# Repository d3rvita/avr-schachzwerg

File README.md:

# AVR-Schachzwerg

The AVR-Schachzwerg is a dedicated chess computer based on the 8-bit microcontroller ATmega88. It is very minimalist like its siblings from the late '70s and the early '80s. Four digit 7-segment display, some buttons and a µC, that's it.

AVR-Schachzwerg was originally developed in 2008 by Andre Adrian, he named it "SHAH". In 2009 (or so) Elektor designed and distributed a PCB of this chess computer (aka "AVR-Max Schachcomputer"). But the button layout was just awful and there ware neither a voltage regulator nor connectors for power supply included. So I attempted to make a better PCB layout... 

Schematic is pretty much originally. I only lowered the resistor values for more display brightness and inserted a voltage regulator together with two connectors for power supply. It can be powered either via USB or a ordinary 8-12 VDC power supply (5.5mm / 2.1mm, plus inside).

The program is a adapted version of Micro-Max 4.8. That is a chess engine by H.G. Müller consisting of less than 2000 characters of C code. Playing strength is around 1300 Elo on the www.schachcomputer.info rating list.

EAGLE was used for creating the schematic (schachzwerg.sch) and layout (schachzwerg.brd). gerber-schachzwerg.zip contains all needed gerber files for PCB production. Bill of material is listed in schachzwerg-bom.txt. All components are designed as THT for easy assembly. It is highly recommended using a socket for the µC. __In order to prevent side effects or even damage don't feed both power supply connectors simultaneously!__

## Schematic

## PCB

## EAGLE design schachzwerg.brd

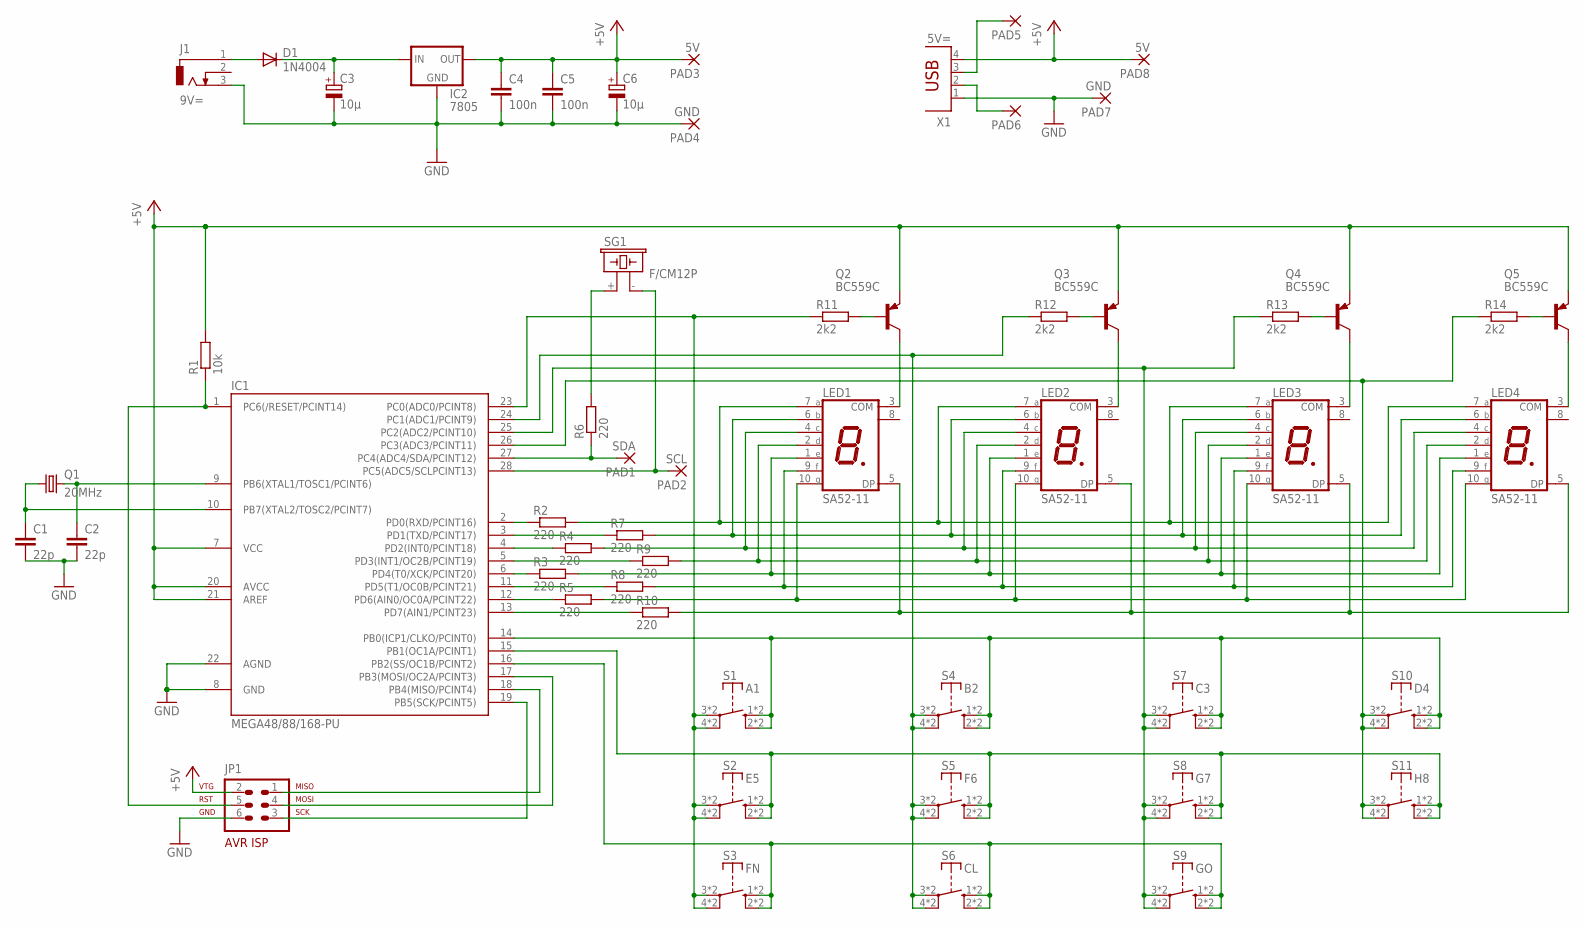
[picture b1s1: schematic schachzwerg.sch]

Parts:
C1, C2: 22p; C025-025X050
C3, C6: 10µ; E2,5-5
C4, C5: 100n; C025-025X050
D1: 1N4004; DO41-10
IC1: MEGA48/88/168-PU; DIL28-3
IC2: 7805; 78XXS
J1: 9V=; DCJ0303
JP1: AVR-ISP-6
LED1, LED2, LED3, LED4: SA52-11
PAD1: SDA; 1,6/0,8
PAD2: SCL; 1,6/0,8
PAD3, PAD8: 5V; 1,6/0,8
PAD4, PAD7: GND; 1,6/0,8
PAD5, PAD6: 1,6/0,8
Q1: 20MHz; HC49/S
Q2, Q3, Q4, Q5: BC559C; TO92-EBC
R1: 10k; 0204/7
R2, R3, R4, R5, R6, R7, R8, R9, R10: 220; 0204/7
R11, R12, R13, R14: 2k2; 0204/7
S1: A1; DT6
S2: E5; DT6
S3: FN; DT6
S4: B2; DT6
S5: F6; DT6
S6: CL; DT6
S7: C3; DT6
S8: G7; DT6
S9: GO; DT6
S10: D4; DT6
S11: H8; DT6
SG1: F/CM12P
X1: 5V=; PN87520

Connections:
+5V: C4.1, C5.1, C6.+, IC1.7 (VCC), IC1.20 (AVCC), IC1.21 (AREF), IC2.OUT, JP1.2, PAD3.1, PAD8.1, Q2.E, Q3.E, Q4.E, Q5.E, R1.2, X1.4
GND: C1.2, C2.2, C3.-, C4.2, C5.2, C6.-, IC1.8 (GND), IC1.22 (AGND), IC2.GND, J1.3, JP1.6, PAD4.1, PAD7.1, X1.1
unnamed: IC1.2 (PD0(RXD/PCINT16)), R2.1
unnamed: IC1.3 (PD1(TXD/PCINT17)), R7.1
unnamed: IC1.4 (PD2(INT0/PCINT18)), R4.1
unnamed: IC1.5 (PD3(INT1/OC2B/PCINT19)), R9.1
unnamed: IC1.6 (PD4(T0/XCK/PCINT20)), R3.1
unnamed: IC1.11 (PD5(T1/OC0B/PCINT21)), R8.1
unnamed: IC1.12 (PD6(AIN0/OC0A/PCINT22)), R5.1
unnamed: IC1.13 (PD7(AIN1/PCINT23)), R10.1
unnamed: LED1.7 (A), LED2.7 (A), LED3.7 (A), LED4.7 (A), R2.2
unnamed: LED1.6 (B), LED2.6 (B), LED3.6 (B), LED4.6 (B), R7.2
unnamed: LED1.4 (C), LED2.4 (C), LED3.4 (C), LED4.4 (C), R4.2
unnamed: LED1.2 (D), LED2.2 (D), LED3.2 (D), LED4.2 (D), R9.2
unnamed: LED1.1 (E), LED2.1 (E), LED3.1 (E), LED4.1 (E), R3.2
unnamed: LED1.9 (F), LED2.9 (F), LED3.9 (F), LED4.9 (F), R8.2
unnamed: LED1.10 (G), LED2.10 (G), LED3.10 (G), LED4.10 (G), R5.2
unnamed: LED1.5 (DP), LED2.5 (DP), LED3.5 (DP), LED4.5 (DP), R10.2
unnamed: LED1.3 (COM), Q2.C
unnamed: LED2.3 (COM), Q3.C
unnamed: LED3.3 (COM), Q4.C
unnamed: LED4.3 (COM), Q5.C
unnamed: Q2.B, R11.2
unnamed: Q3.B, R12.2
unnamed: Q4.B, R13.2
unnamed: Q5.B, R14.2
unnamed: C2.1, IC1.9 (PB6(XTAL1/TOSC1/PCINT6)), Q1.2
unnamed: PAD6.1, X1.2
unnamed: R6.2, SG1.+ (1)
unnamed: IC1.28 (PC5(ADC5/SCLPCINT13)), PAD2.1, SG1.- (2)
unnamed: D1.A, J1.1
unnamed: IC1.1 (PC6(/RESET/PCINT14)), JP1.5, R1.1
unnamed: IC1.19 (PB5(SCK/PCINT5)), JP1.3
unnamed: IC1.17 (PB3(MOSI/OC2A/PCINT3)), JP1.4
unnamed: IC1.18 (PB4(MISO/PCINT4)), JP1.1
unnamed: IC1.23 (PC0(ADC0/PCINT8)), R11.1, S1.3, S1.4, S1.7, S1.8, S2.3, S2.4, S2.7, S2.8, S3.3, S3.4, S3.7, S3.8
unnamed: IC1.24 (PC1(ADC1/PCINT9)), R12.1, S4.3, S4.4, S4.7, S4.8, S5.3, S5.4, S5.7, S5.8, S6.3, S6.4, S6.7, S6.8
unnamed: IC1.25 (PC2(ADC2/PCINT10)), R13.1, S7.3, S7.4, S7.7, S7.8, S8.3, S8.4, S8.7, S8.8, S9.3, S9.4, S9.7, S9.8
unnamed: IC1.26 (PC3(ADC3/PCINT11)), R14.1, S10.3, S10.4, S10.7, S10.8, S11.3, S11.4, S11.7, S11.8
unnamed: IC1.14 (PB0(ICP1/CLKO/PCINT0)), S1.1 (S), S1.2 (S), S1.5 (S), S1.6 (S), S4.1 (S), S4.2 (S), S4.5 (S), S4.6 (S), S7.1 (S), S7.2 (S), S7.5 (S), S7.6 (S), S10.1 (S), S10.2 (S), S10.5 (S), S10.6 (S)
unnamed: PAD5.1, X1.3
unnamed: IC1.15 (PB1(OC1A/PCINT1)), S2.1 (S), S2.2 (S), S2.5 (S), S2.6 (S), S5.1 (S), S5.2 (S), S5.5 (S), S5.6 (S), S8.1 (S), S8.2 (S), S8.5 (S), S8.6 (S), S11.1 (S), S11.2 (S), S11.5 (S), S11.6 (S)
unnamed: IC1.16 (PB2(SS/OC1B/PCINT2)), S3.1 (S), S3.2 (S), S3.5 (S), S3.6 (S), S6.1 (S), S6.2 (S), S6.5 (S), S6.6 (S), S9.1 (S), S9.2 (S), S9.5 (S), S9.6 (S)
unnamed: C3.+, D1.C, IC2.IN
unnamed: C1.1, IC1.10 (PB7(XTAL2/TOSC2/PCINT7)), Q1.1
unnamed: IC1.27 (PC4(ADC4/SDA/PCINT12)), PAD1.1, R6.1

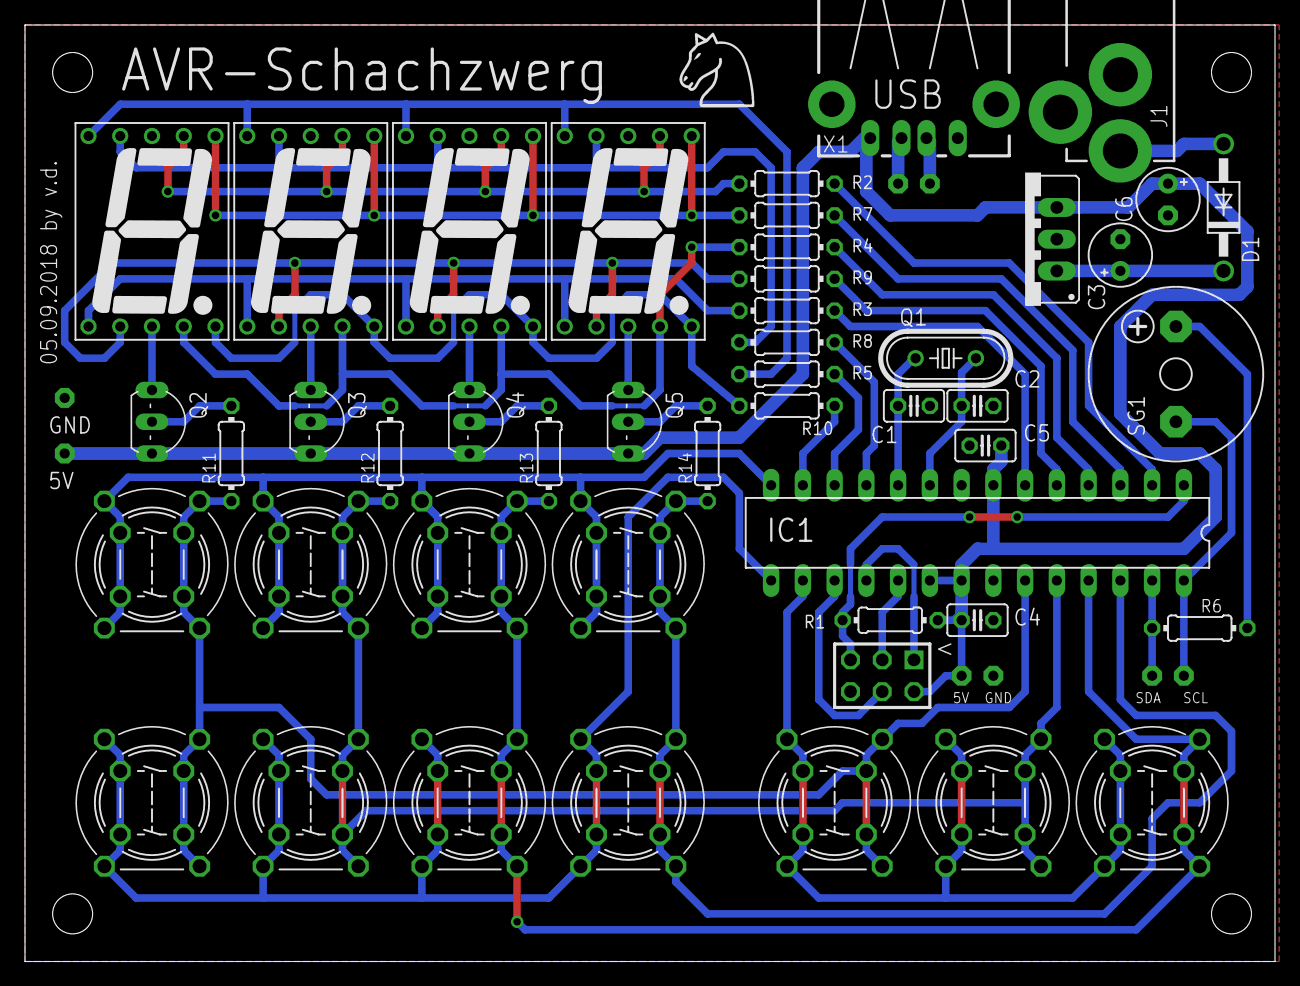
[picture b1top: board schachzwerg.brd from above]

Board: 2 copper layers, 100.0 x 74.9 mm, 55 parts (0 on the bottom side), 46 nets.

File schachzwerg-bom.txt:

Part       Value               Device             Package        Description                                                 
C1*        22p                 C-EU025-025X050    C025-025X050   CAPACITOR, European symbol                                  
C2*        22p                 C-EU025-025X050    C025-025X050   CAPACITOR, European symbol                                  
C3         10µ                 CPOL-EUE2.5-5      E2,5-5         POLARIZED CAPACITOR, European symbol                        
C4         100n                C-EU025-025X050    C025-025X050   CAPACITOR, European symbol                                  
C5         100n                C-EU025-025X050    C025-025X050   CAPACITOR, European symbol                                  
C6         10µ                 CPOL-EUE2.5-5      E2,5-5         POLARIZED CAPACITOR, European symbol                        
D1         1N4004              1N4004             DO41-10        DIODE                                                       
IC1**      MEGA48/88/168-PU    MEGA48/88/168-PU   DIL28-3        MICROCONTROLLER                                             
IC2        7805                78XXS              TO220          VOLTAGE REGULATOR                                           
J1         9V=                 DCJ0303            DCJ0303        DC POWER JACK (5.5mm / 2.1mm)                               
JP1        AVR-ISP-6           AVR-ISP-6          AVR-ISP-6      AVR ISP-6 Serial Programming Header                         
LED1       SA52-11             7-SEG_SA52-11      SA52-11        Kingbright 14.2mm (0.56 INCH) SINGLE DIGIT NUMERIC DUISPLAY 
LED2       SA52-11             7-SEG_SA52-11      SA52-11        Kingbright 14.2mm (0.56 INCH) SINGLE DIGIT NUMERIC DUISPLAY 
LED3       SA52-11             7-SEG_SA52-11      SA52-11        Kingbright 14.2mm (0.56 INCH) SINGLE DIGIT NUMERIC DUISPLAY 
LED4       SA52-11             7-SEG_SA52-11      SA52-11        Kingbright 14.2mm (0.56 INCH) SINGLE DIGIT NUMERIC DUISPLAY 
Q1*        20MHz               CRYSTAL            HC49/S         CRYSTAL                                                     
Q2         BC559C              BC559C             TO92-EBC       PNP Transistor                                             
Q3         BC559C              BC559C             TO92-EBC       PNP Transistor                                             
Q4         BC559C              BC559C             TO92-EBC       PNP Transistor                                             
Q5         BC559C              BC559C             TO92-EBC       PNP Transistor                                             
R1         10k                 R-EU_0204/7        0204/7         RESISTOR, European symbol                                   
R2         220                 R-EU_0204/7        0204/7         RESISTOR, European symbol                                   
R3         220                 R-EU_0204/7        0204/7         RESISTOR, European symbol                                   
R4         220                 R-EU_0204/7        0204/7         RESISTOR, European symbol                                   
R5         220                 R-EU_0204/7        0204/7         RESISTOR, European symbol                                   
R6***      220                 R-EU_0204/7        0204/7         RESISTOR, European symbol                                   
R7         220                 R-EU_0204/7        0204/7         RESISTOR, European symbol                                   
R8         220                 R-EU_0204/7        0204/7         RESISTOR, European symbol                                   
R9         220                 R-EU_0204/7        0204/7         RESISTOR, European symbol                                   
R10        220                 R-EU_0204/7        0204/7         RESISTOR, European symbol                                   
R11        2k2                 R-EU_0204/7        0204/7         RESISTOR, European symbol                                   
R12        2k2                 R-EU_0204/7        0204/7         RESISTOR, European symbol                                   
R13        2k2                 R-EU_0204/7        0204/7         RESISTOR, European symbol                                   
R14        2k2                 R-EU_0204/7        0204/7         RESISTOR, European symbol                                   
S1         A1                  3FTH9 / DT6        3FTH9 / DT6    SWITCH, MULTIMEC 3FTH9 (10.16x7.62mm) OR ITT DT6 (5x5mm)    
S2         E5                  3FTH9 / DT6        3FTH9 / DT6    SWITCH, MULTIMEC 3FTH9 (10.16x7.62mm) OR ITT DT6 (5x5mm)    
S3         FN                  3FTH9 / DT6        3FTH9 / DT6    SWITCH, MULTIMEC 3FTH9 (10.16x7.62mm) OR ITT DT6 (5x5mm)    
S4         B2                  3FTH9 / DT6        3FTH9 / DT6    SWITCH, MULTIMEC 3FTH9 (10.16x7.62mm) OR ITT DT6 (5x5mm)    
S5         F6                  3FTH9 / DT6        3FTH9 / DT6    SWITCH, MULTIMEC 3FTH9 (10.16x7.62mm) OR ITT DT6 (5x5mm)    
S6         CL                  3FTH9 / DT6        3FTH9 / DT6    SWITCH, MULTIMEC 3FTH9 (10.16x7.62mm) OR ITT DT6 (5x5mm)    
S7         C3                  3FTH9 / DT6        3FTH9 / DT6    SWITCH, MULTIMEC 3FTH9 (10.16x7.62mm) OR ITT DT6 (5x5mm)    
S8         G7                  3FTH9 / DT6        3FTH9 / DT6    SWITCH, MULTIMEC 3FTH9 (10.16x7.62mm) OR ITT DT6 (5x5mm)    
S9         GO                  3FTH9 / DT6        3FTH9 / DT6    SWITCH, MULTIMEC 3FTH9 (10.16x7.62mm) OR ITT DT6 (5x5mm)    
S10        D4                  3FTH9 / DT6        3FTH9 / DT6    SWITCH, MULTIMEC 3FTH9 (10.16x7.62mm) OR ITT DT6 (5x5mm)    
S11        H8                  3FTH9 / DT6        3FTH9 / DT6    SWITCH, MULTIMEC 3FTH9 (10.16x7.62mm) OR ITT DT6 (5x5mm)    
SG1***     F/CM12P             F/CM12P            F/CM12P        BUZZER                                                      
X1         5V=                 PN87520            PN87520        USB-A connector                                             

*optional for higher speed
**socket is recommended
***not used yet

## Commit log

2019-01-22 Create LICENSE
